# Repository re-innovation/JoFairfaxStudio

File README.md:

# JoFairfaxStudio
A repository for projects for Jo Fairfax Studio

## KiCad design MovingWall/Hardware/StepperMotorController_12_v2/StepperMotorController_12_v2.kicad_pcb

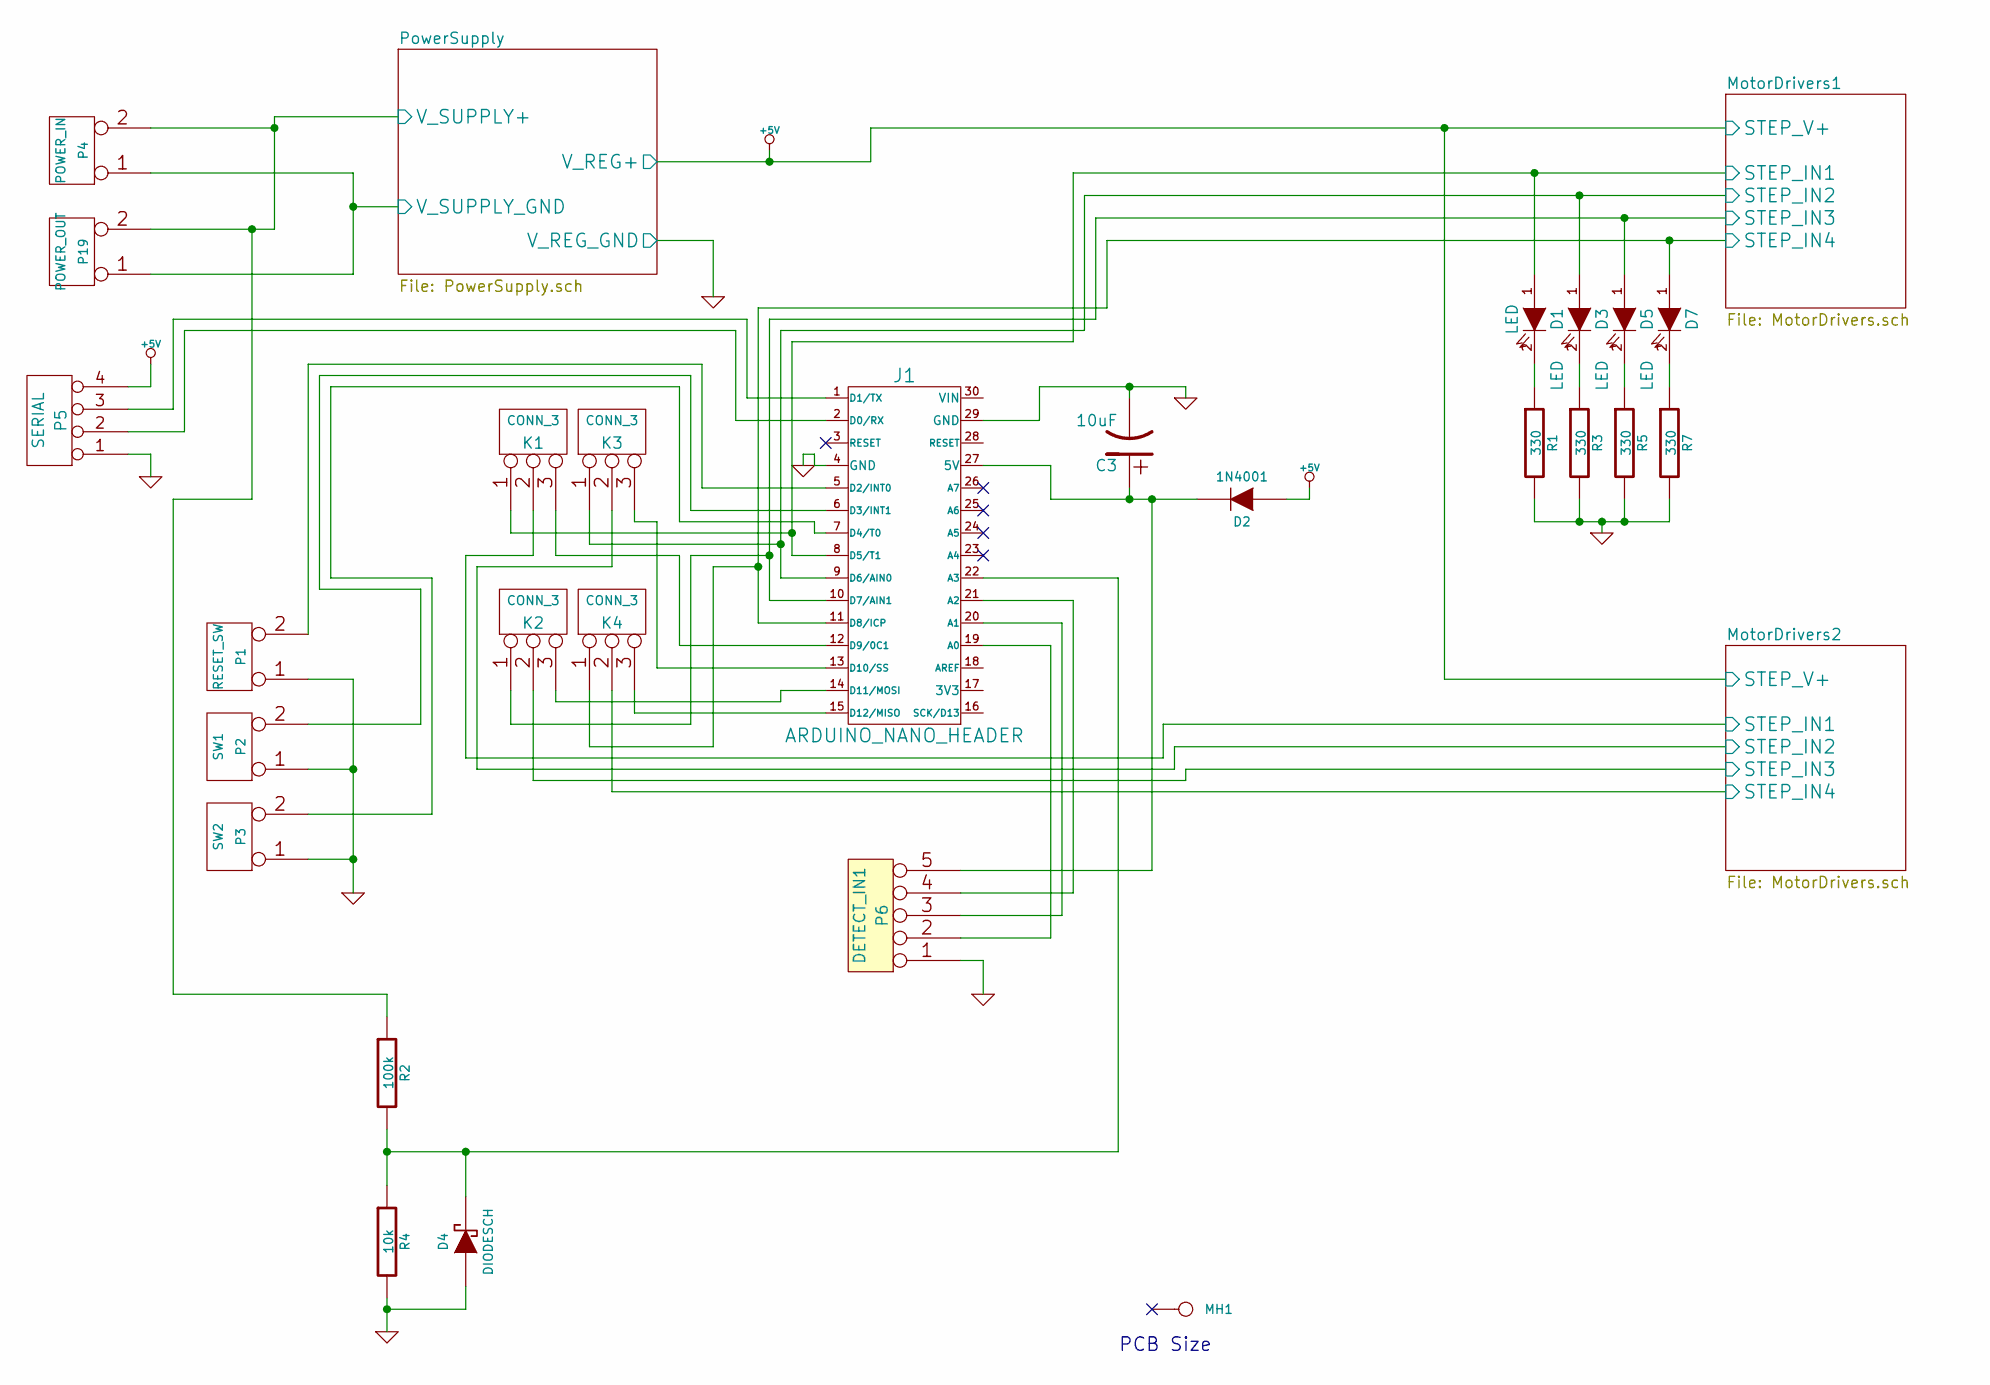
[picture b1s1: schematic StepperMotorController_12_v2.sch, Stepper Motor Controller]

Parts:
C3: 10uF; C2V8_large_pads; Manufacturer Part No Value
D1, D3, D5, D7: LED; led-LED3MM_matt; Manufacturer Part No Value
D2: 1N4001; D3_lg_pad
D4: DIODESCH; D3_lg_pad
J1: ARDUINO_NANO_HEADER; DIP_30_600_NANO
K1, K2, K3, K4: CONN_3; SIL-3_SOLDER
MH1: CONN_1; PCB_85x120_4hole
P1: RESET_SW; SIL-2_screw_terminal
P2: SW1; SIL-2_lg_pad_1mm
P3: SW2; SIL-2_lg_pad_1mm
P4: POWER_IN; SIL-2_screw_terminal
P5: SERIAL; SIL-4_large_pad
P6: DETECT_IN1; SIL-5_JST_5WAY
P19: POWER_OUT; SIL-2_screw_terminal; Manufacturer Part No Value
R1, R3, R5, R7: 330; R3-LARGE_PADS_0_8_hole; Manufacturer Part No Value
R2: 100k; R3-LARGE_PADS_0_8_hole; Manufacturer Part No Value
R4: 10k; R3-LARGE_PADS_0_8_hole; Manufacturer Part No Value

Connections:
/MotorDrivers1/STEP_IN1: D1.1 (A), J1.8 (D5/T1), K1.1; also elsewhere on the board
/MotorDrivers1/STEP_IN2: D3.1 (A), J1.9 (D6/AIN0), K3.1; also elsewhere on the board
/MotorDrivers1/STEP_IN3: D5.1 (A), J1.10 (D7/AIN1), K2.1; also elsewhere on the board
/MotorDrivers1/STEP_IN4: D7.1 (A), J1.11 (D8/ICP), K4.1; also elsewhere on the board
/MotorDrivers2/STEP_IN1: K1.2 (PM); also elsewhere on the board
/MotorDrivers2/STEP_IN2: K3.2 (PM); also elsewhere on the board
/MotorDrivers2/STEP_IN3: K2.2 (PM); also elsewhere on the board
/MotorDrivers2/STEP_IN4: K4.2 (PM); also elsewhere on the board
/PowerSupply/V_SUPPLY+: P4.2 (PM), P19.2 (PM), R2.1; also elsewhere on the board
/PowerSupply/V_SUPPLY_GND: P4.1, P19.1; also elsewhere on the board
GND: C3.2, D4.2 (A), J1.4 (GND), J1.29 (GND), P1.1, P2.1, P3.1, P5.1, P6.1, R1.2, R3.2, R4.2, R5.2, R7.2; also elsewhere on the board
unnamed: D1.2 (K), R1.1
unnamed: D3.2 (K), R3.1
unnamed: D4.1 (K), J1.22 (A3), R2.2, R4.1
unnamed: D5.2 (K), R5.1
unnamed: D7.2 (K), R7.1
unnamed: J1.1 (D1/TX), P5.3
unnamed: J1.2 (D0/RX), P5.2
unnamed: J1.5 (D2/INT0), P1.2 (PM)
unnamed: J1.6 (D3/INT1), P2.2 (PM)
unnamed: J1.7 (D4/T0), P3.2 (PM)
unnamed: J1.12 (D9/0C1), K1.3
unnamed: J1.13 (D10/SS), K3.3
unnamed: J1.14 (D11/MOSI), K2.3
unnamed: J1.15 (D12/MISO), K4.3
unnamed: J1.19 (A0), P6.2
unnamed: J1.20 (A1), P6.3
unnamed: J1.21 (A2), P6.4

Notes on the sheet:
PCB Size

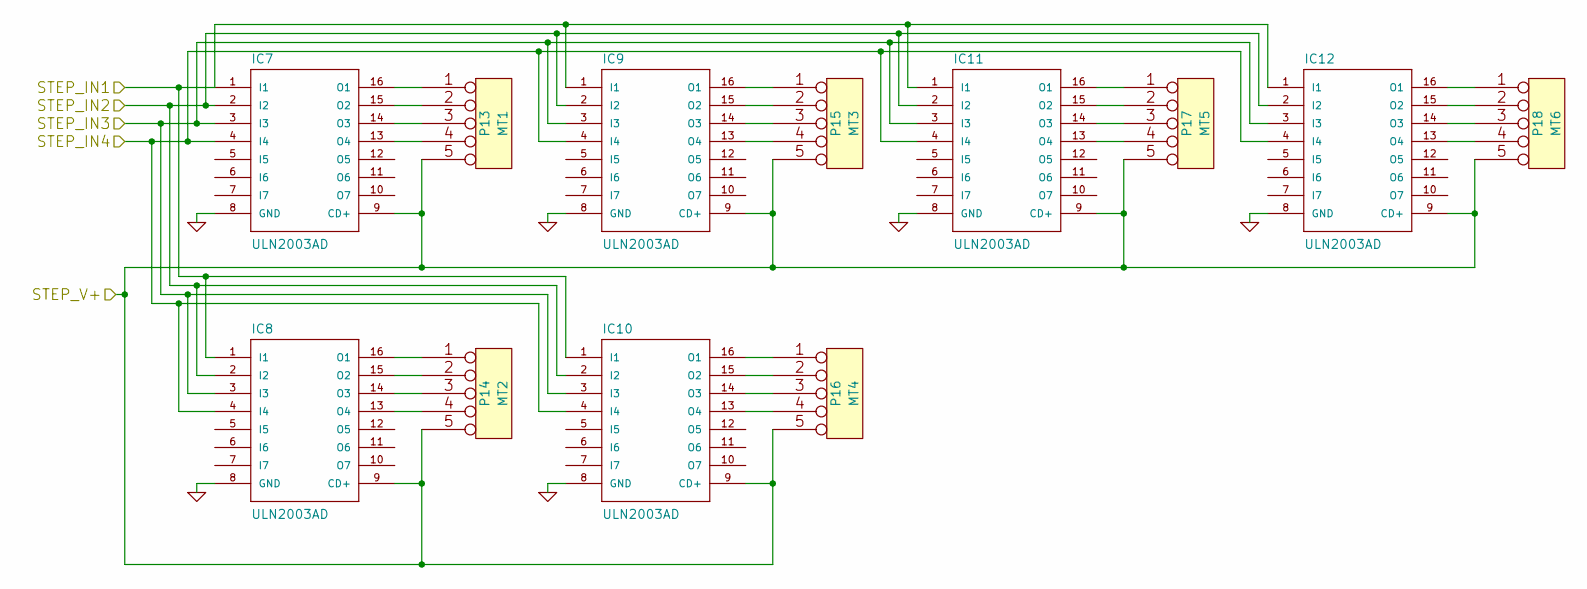
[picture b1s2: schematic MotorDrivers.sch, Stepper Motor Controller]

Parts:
IC1, IC2, IC3, IC4, IC5, IC6: ULN2003AD; DIP-16__300_ELL
P7: MT1; SIL-5_JST_5WAY
P8: MT2; SIL-5_JST_5WAY
P9: MT3; SIL-5_JST_5WAY
P10: MT4; SIL-5_JST_5WAY
P11: MT5; SIL-5_JST_5WAY
P12: MT6; SIL-5_JST_5WAY

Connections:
/MotorDrivers1/STEP_IN1: IC1.1 (I1), IC2.1 (I1), IC3.1 (I1), IC4.1 (I1), IC5.1 (I1), IC6.1 (I1); also elsewhere on the board
/MotorDrivers1/STEP_IN2: IC1.2 (I2), IC2.2 (I2), IC3.2 (I2), IC4.2 (I2), IC5.2 (I2), IC6.2 (I2); also elsewhere on the board
/MotorDrivers1/STEP_IN3: IC1.3 (I3), IC2.3 (I3), IC3.3 (I3), IC4.3 (I3), IC5.3 (I3), IC6.3 (I3); also elsewhere on the board
/MotorDrivers1/STEP_IN4: IC1.4 (I4), IC2.4 (I4), IC3.4 (I4), IC4.4 (I4), IC5.4 (I4), IC6.4 (I4); also elsewhere on the board
GND: IC1.8 (GND), IC2.8 (GND), IC3.8 (GND), IC4.8 (GND), IC5.8 (GND), IC6.8 (GND); also elsewhere on the board
unnamed: IC1.13 (O4), P7.4
unnamed: IC1.14 (O3), P7.3
unnamed: IC1.15 (O2), P7.2
unnamed: IC1.16 (O1), P7.1
unnamed: IC2.13 (O4), P8.4
unnamed: IC2.14 (O3), P8.3
unnamed: IC2.15 (O2), P8.2
unnamed: IC2.16 (O1), P8.1
unnamed: IC3.13 (O4), P9.4
unnamed: IC3.14 (O3), P9.3
unnamed: IC3.15 (O2), P9.2
unnamed: IC3.16 (O1), P9.1
unnamed: IC4.13 (O4), P10.4
unnamed: IC4.14 (O3), P10.3
unnamed: IC4.15 (O2), P10.2
unnamed: IC4.16 (O1), P10.1
unnamed: IC5.13 (O4), P11.4
unnamed: IC5.14 (O3), P11.3
unnamed: IC5.15 (O2), P11.2
unnamed: IC5.16 (O1), P11.1
unnamed: IC6.13 (O4), P12.4
unnamed: IC6.14 (O3), P12.3
unnamed: IC6.15 (O2), P12.2
unnamed: IC6.16 (O1), P12.1

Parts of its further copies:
IC7, IC8, IC9, IC10, IC11, IC12: ULN2003AD; DIP-16__300_ELL
P13: MT1; SIL-5_JST_5WAY
P14: MT2; SIL-5_JST_5WAY
P15: MT3; SIL-5_JST_5WAY
P16: MT4; SIL-5_JST_5WAY
P17: MT5; SIL-5_JST_5WAY
P18: MT6; SIL-5_JST_5WAY

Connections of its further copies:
/MotorDrivers2/STEP_IN1: IC7.1 (I1), IC8.1 (I1), IC9.1 (I1), IC10.1 (I1), IC11.1 (I1), IC12.1 (I1); also elsewhere on the board
/MotorDrivers2/STEP_IN2: IC7.2 (I2), IC8.2 (I2), IC9.2 (I2), IC10.2 (I2), IC11.2 (I2), IC12.2 (I2); also elsewhere on the board
/MotorDrivers2/STEP_IN3: IC7.3 (I3), IC8.3 (I3), IC9.3 (I3), IC10.3 (I3), IC11.3 (I3), IC12.3 (I3); also elsewhere on the board
/MotorDrivers2/STEP_IN4: IC7.4 (I4), IC8.4 (I4), IC9.4 (I4), IC10.4 (I4), IC11.4 (I4), IC12.4 (I4); also elsewhere on the board
GND: IC7.8 (GND), IC8.8 (GND), IC9.8 (GND), IC10.8 (GND), IC11.8 (GND), IC12.8 (GND); also elsewhere on the board
unnamed: IC7.13 (O4), P13.4
unnamed: IC7.14 (O3), P13.3
unnamed: IC7.15 (O2), P13.2
unnamed: IC7.16 (O1), P13.1
unnamed: IC8.13 (O4), P14.4
unnamed: IC8.14 (O3), P14.3
unnamed: IC8.15 (O2), P14.2
unnamed: IC8.16 (O1), P14.1
unnamed: IC9.13 (O4), P15.4
unnamed: IC9.14 (O3), P15.3
unnamed: IC9.15 (O2), P15.2
unnamed: IC9.16 (O1), P15.1
unnamed: IC10.13 (O4), P16.4
unnamed: IC10.14 (O3), P16.3
unnamed: IC10.15 (O2), P16.2
unnamed: IC10.16 (O1), P16.1
unnamed: IC11.13 (O4), P17.4
unnamed: IC11.14 (O3), P17.3
unnamed: IC11.15 (O2), P17.2
unnamed: IC11.16 (O1), P17.1
unnamed: IC12.13 (O4), P18.4
unnamed: IC12.14 (O3), P18.3
unnamed: IC12.15 (O2), P18.2
unnamed: IC12.16 (O1), P18.1

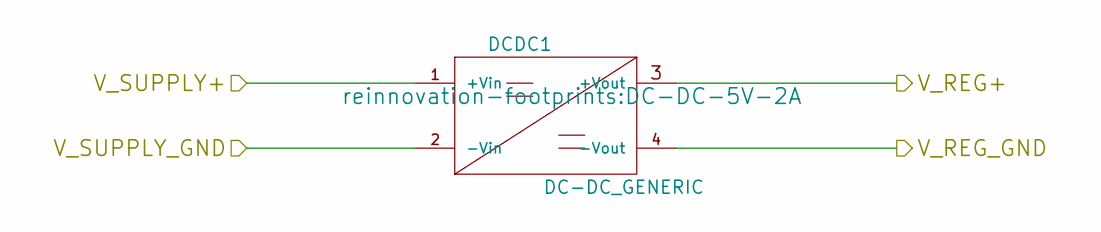
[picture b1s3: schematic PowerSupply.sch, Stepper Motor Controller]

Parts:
DCDC1: DC-DC_GENERIC; DC-DC-5V-2A

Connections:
/PowerSupply/V_SUPPLY+: DCDC1.1 (+Vin); also elsewhere on the board
/PowerSupply/V_SUPPLY_GND: DCDC1.2 (-Vin); also elsewhere on the board
GND: DCDC1.4 (-Vout); also elsewhere on the board

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
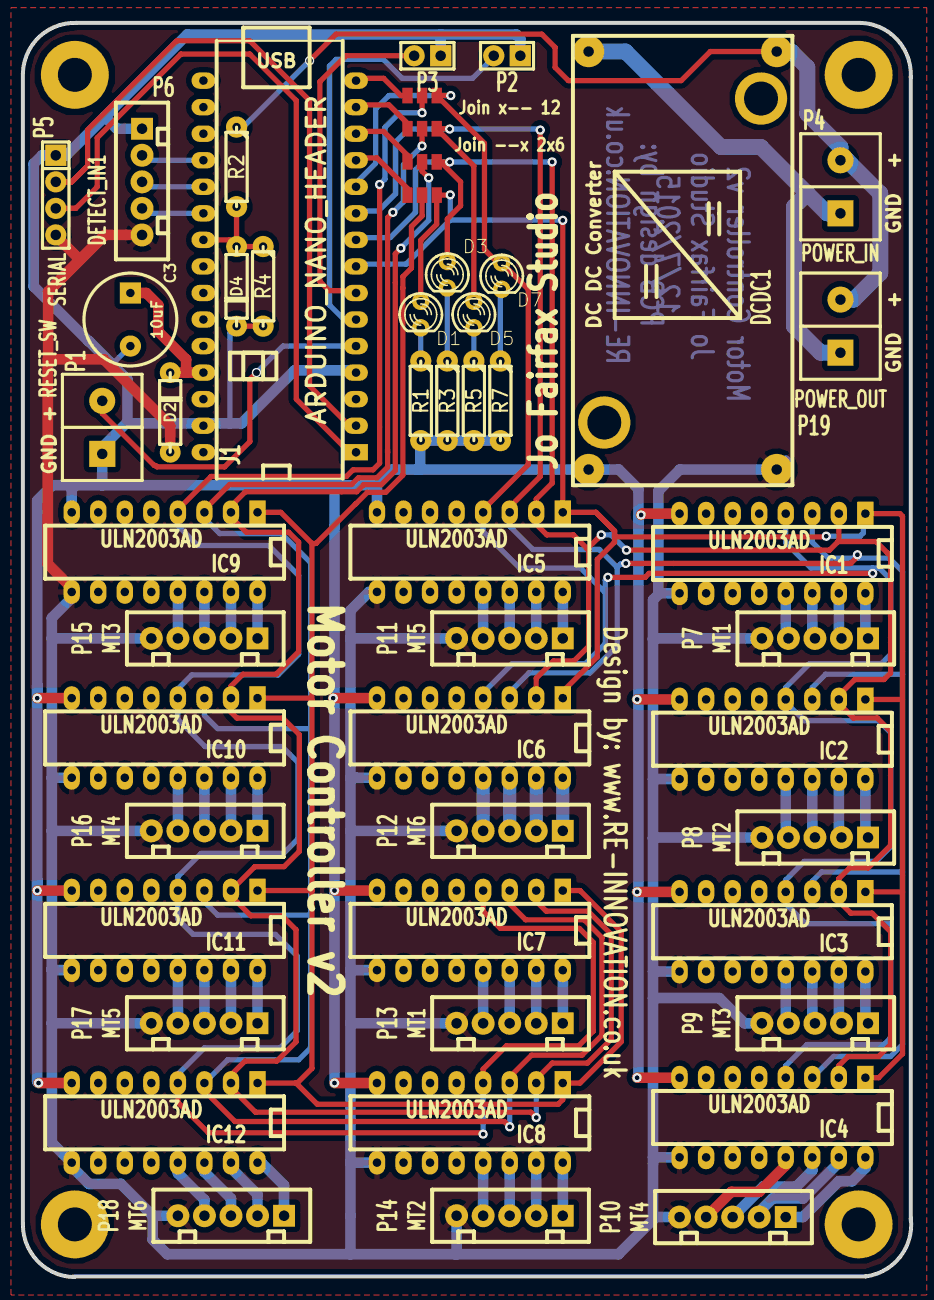
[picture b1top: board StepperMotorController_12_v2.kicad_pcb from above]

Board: 2 copper layers, 85.0 x 120.0 mm, 51 parts (0 on the bottom side), 78 nets.

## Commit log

2015-11-06 Create PoetryWall
2015-11-06 Create MovingWall
2015-11-06 Upload of Moving Wall and Poetry Wall Initial commits
2015-11-06 Master Slave code added Poetry Wall
2015-11-06 Master code update from Matt
2015-11-09 Code for master updated
    Master unit works as controller. Need to add stepper code for master
    unit (copy from slave code)
2015-11-11 Slave unit uses IR feedback
2015-11-20 Added stepper IR tester
2015-11-20 Added spool pattern SVG
2015-11-20 Completed slave unit code
2015-11-20 Moved motor control to own class
2015-11-20 Moved command processing to own module
2015-11-20 Fixed some comments
2015-11-20 Master unit uses word reel class
2015-12-04 Demo Software complete
2015-12-11 Fixed serial bugs and added timeout
2015-12-18 Motors move simultaneously. No blocking code.
2016-03-11 Calibration routines
2016-04-14 Latest motion control code
2016-05-27 Code updates
    Solar birdsong unit - v13 now working
    Update of poetry wall changes
2016-11-28 Changed birdsong files
2017-04-05 Updated with changes
2021-04-25 updated with basic motor controller for MAP
